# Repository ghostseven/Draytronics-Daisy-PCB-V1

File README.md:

# Draytronics-Daisy-PCB-V1

An open source macro pad with rotary encoders and under glow, designed to be easily built with (mostly) through hole components. More info / kits / PCB designs available at https://www.draytronics.co.uk/daisy

\

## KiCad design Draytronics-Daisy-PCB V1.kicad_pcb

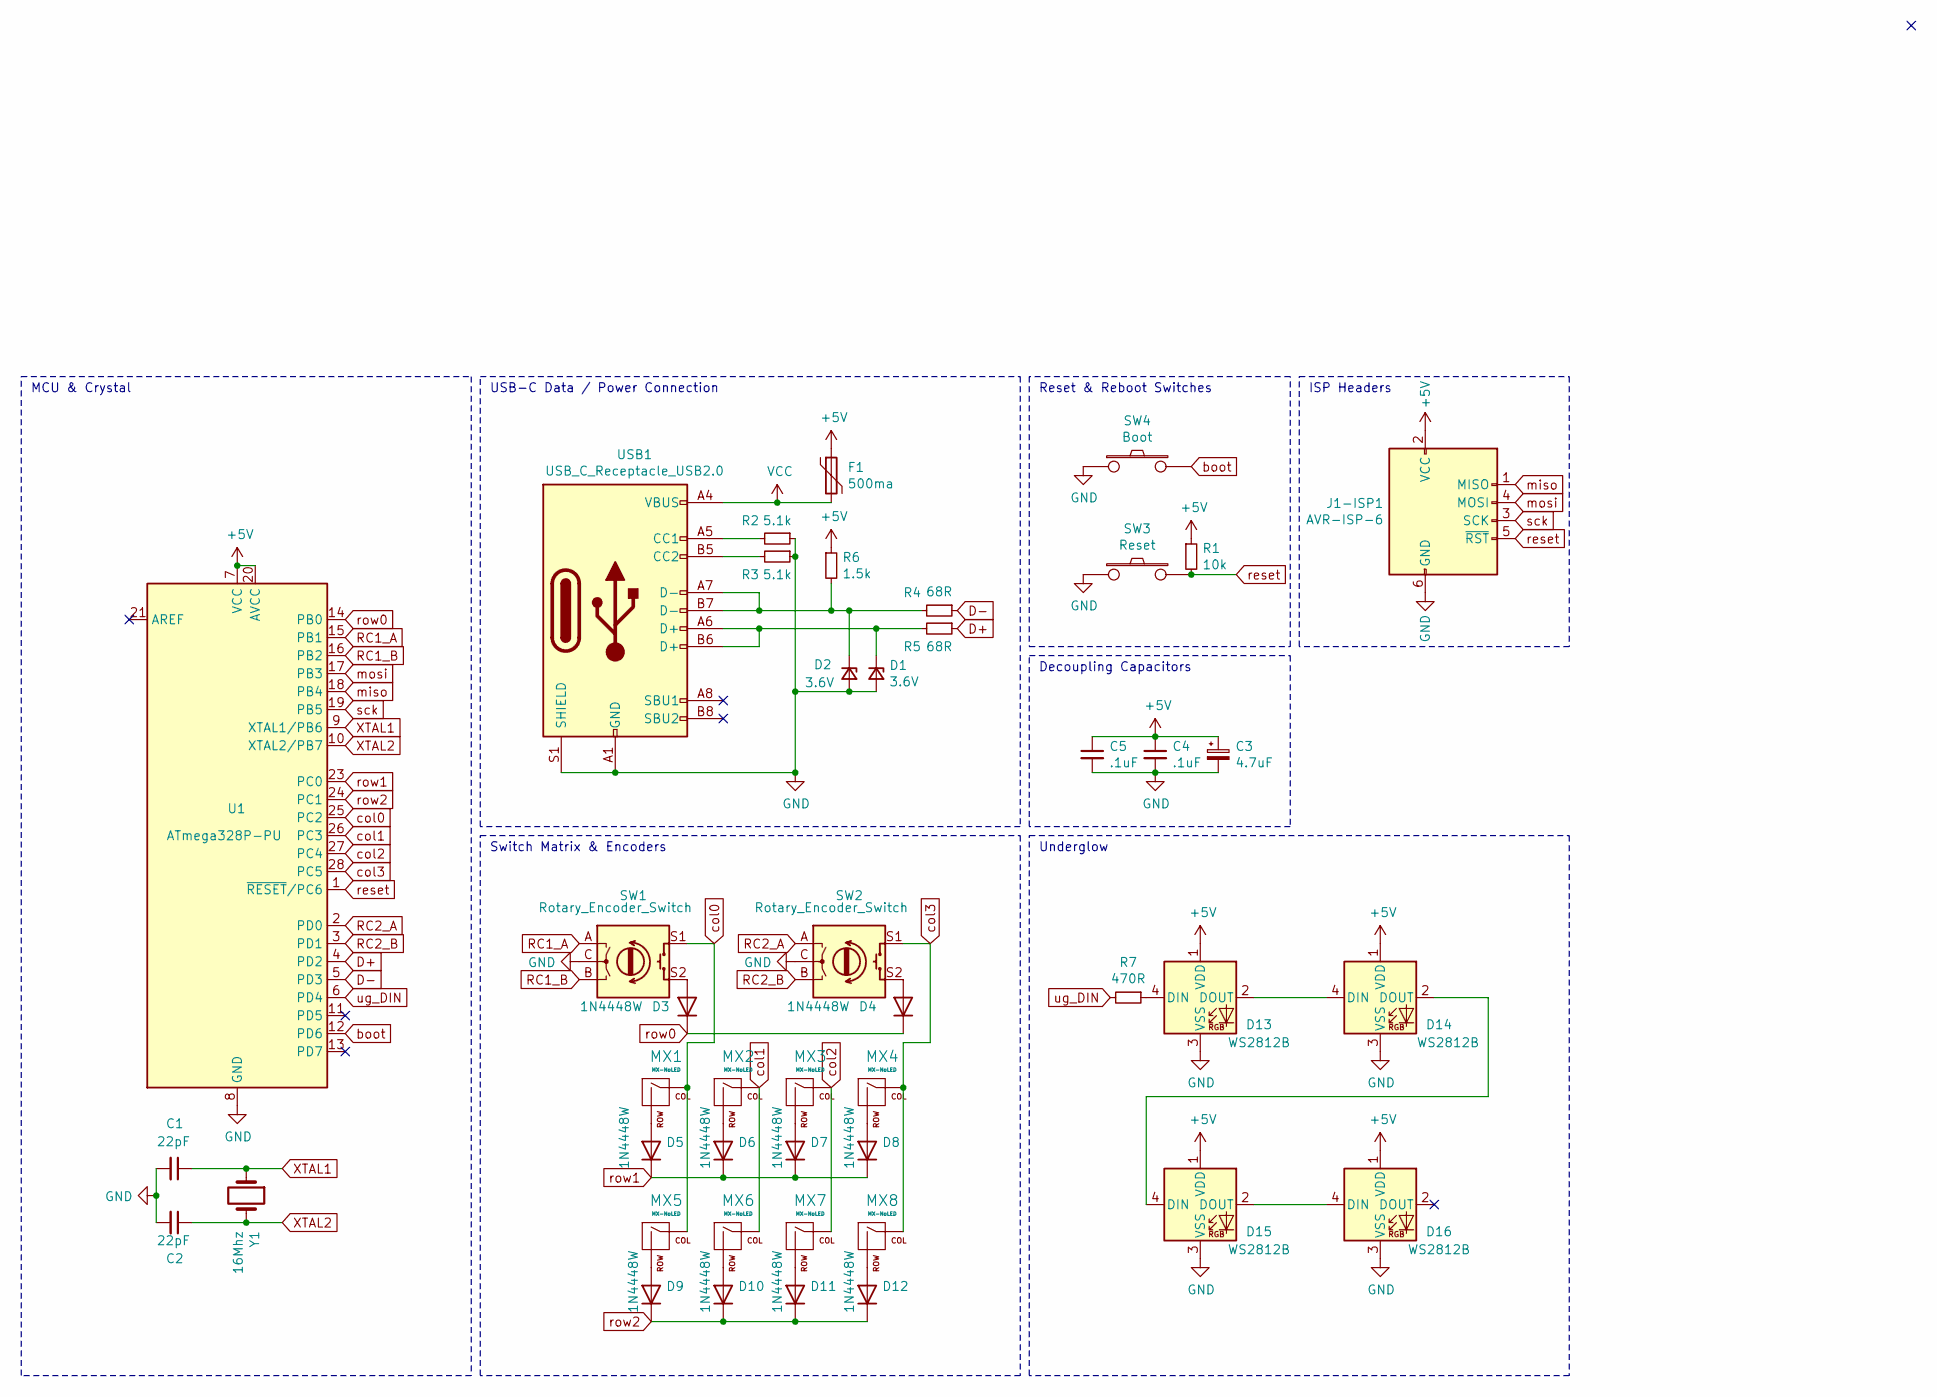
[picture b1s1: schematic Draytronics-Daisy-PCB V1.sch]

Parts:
C1, C2: 22pF; C_Disc_D3.0mm_W1.6mm_P2.50mm
C3: 4.7uF; CP_Radial_D4.0mm_P1.50mm
C4, C5: .1uF; C_Disc_D3.0mm_W1.6mm_P2.50mm
D1, D2: 3.6V; D_DO-35_SOD27_P5.08mm_Horizontal
D3, D4, D5, D6, D7, D8, D9, D10, D11, D12: 1N4448W; D_DO-35_SOD27_P5.08mm_Horizontal
D13, D14, D15, D16: WS2812B; LED_WS2812B_PLCC4_5.0x5.0mm_P3.2mm
F1: 500ma; polyfuse_5.1mm
J1-ISP1: AVR-ISP-6; IDC-Header_2x03_P2.54mm_Vertical
MX1, MX2, MX3, MX4, MX5, MX6, MX7, MX8: MX-NoLED; MXOnly-1U-NoLED
R1: 10k; R_Axial_DIN0204_L3.6mm_D1.6mm_P7.62mm_Horizontal
R2, R3: 5.1k; R_Axial_DIN0204_L3.6mm_D1.6mm_P7.62mm_Horizontal
R4, R5: 68R; R_Axial_DIN0204_L3.6mm_D1.6mm_P7.62mm_Horizontal
R6: 1.5k; R_Axial_DIN0204_L3.6mm_D1.6mm_P7.62mm_Horizontal
R7: 470R; R_Axial_DIN0204_L3.6mm_D1.6mm_P7.62mm_Horizontal
SW1, SW2: Rotary_Encoder_Switch; RotaryEncoder_Alps_EC11E-Switch_Vertical_H20mm
SW3: Reset; SW_PUSH_6mm
SW4: Boot; SW_PUSH_6mm
U1: ATmega328P-PU; DIP-28_W7.62mm
USB1: USB_C_Receptacle_USB2.0; USB_C_GCT_USB4085
Y1: 16Mhz; Crystal_HC49-U_Vertical

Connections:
+5V: C3.1, C4.1, C5.1, D13.1 (VDD), D14.1 (VDD), D15.1 (VDD), D16.1 (VDD), F1.1, J1-ISP1.2 (VCC), R1.1, R6.1, U1.7 (VCC), U1.20 (AVCC)
D+: R5.1, U1.4 (PD2)
D-: R4.1, U1.5 (PD3)
GND: C1.2, C2.2, C3.2, C4.2, C5.2, D1.2 (A), D2.2 (A), D13.3 (VSS), D14.3 (VSS), D15.3 (VSS), D16.3 (VSS), J1-ISP1.6 (GND), R2.1, R3.1, SW1.C, SW2.C, SW3.1, SW4.1, U1.8 (GND), U1.22 (GND), USB1.A1 (GND), USB1.A12 (GND), USB1.B1 (GND), USB1.B12 (GND), USB1.S1 (SHIELD)
unnamed: D1.1 (K), R5.2, USB1.A6 (D+), USB1.B6 (D+)
unnamed: D2.1 (K), R4.2, R6.2, USB1.A7 (D-), USB1.B7 (D-)
unnamed: D3.2 (A), SW1.S2
unnamed: D4.2 (A), SW2.S2
unnamed: D5.2 (A), MX1.2 (ROW)
unnamed: D6.2 (A), MX2.2 (ROW)
unnamed: D7.2 (A), MX3.2 (ROW)
unnamed: D8.2 (A), MX4.2 (ROW)
unnamed: D9.2 (A), MX5.2 (ROW)
unnamed: D10.2 (A), MX6.2 (ROW)
unnamed: D11.2 (A), MX7.2 (ROW)
unnamed: D12.2 (A), MX8.2 (ROW)
unnamed: D13.2 (DOUT), D14.4 (DIN)
unnamed: D13.4 (DIN), R7.1
unnamed: D14.2 (DOUT), D15.4 (DIN)
unnamed: D15.2 (DOUT), D16.4 (DIN)
unnamed: R2.2, USB1.A5 (CC1)
unnamed: R3.2, USB1.B5 (CC2)
RC1_A: SW1.A, U1.15 (PB1)
RC1_B: SW1.B, U1.16 (PB2)
RC2_A: SW2.A, U1.2 (PD0)
RC2_B: SW2.B, U1.3 (PD1)
VCC: F1.2, USB1.A4 (VBUS), USB1.A9 (VBUS), USB1.B4 (VBUS), USB1.B9 (VBUS)
XTAL1: C1.1, U1.9 (XTAL1/PB6), Y1.1
XTAL2: C2.1, U1.10 (XTAL2/PB7), Y1.2
boot: SW4.2, U1.12 (PD6)
col0: MX1.1 (COL), MX5.1 (COL), SW1.S1, U1.25 (PC2)
col1: MX2.1 (COL), MX6.1 (COL), U1.26 (PC3)
col2: MX3.1 (COL), MX7.1 (COL), U1.27 (PC4)
col3: MX4.1 (COL), MX8.1 (COL), SW2.S1, U1.28 (PC5)
miso: J1-ISP1.1 (MISO), U1.18 (PB4)
mosi: J1-ISP1.4 (MOSI), U1.17 (PB3)
reset: J1-ISP1.5 (~RST), R1.2, SW3.2, U1.1 (~RESET~/PC6)
row0: D3.1 (K), D4.1 (K), U1.14 (PB0)
row1: D5.1 (K), D6.1 (K), D7.1 (K), D8.1 (K), U1.23 (PC0)
row2: D9.1 (K), D10.1 (K), D11.1 (K), D12.1 (K), U1.24 (PC1)
sck: J1-ISP1.3 (SCK), U1.19 (PB5)
ug_DIN: R7.2, U1.6 (PD4)

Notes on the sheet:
USB-C Data / Power Connection
MCU & Crystal
Reset & Reboot Switches
ISP Headers
Decoupling Capacitors
Switch Matrix & Encoders
Underglow

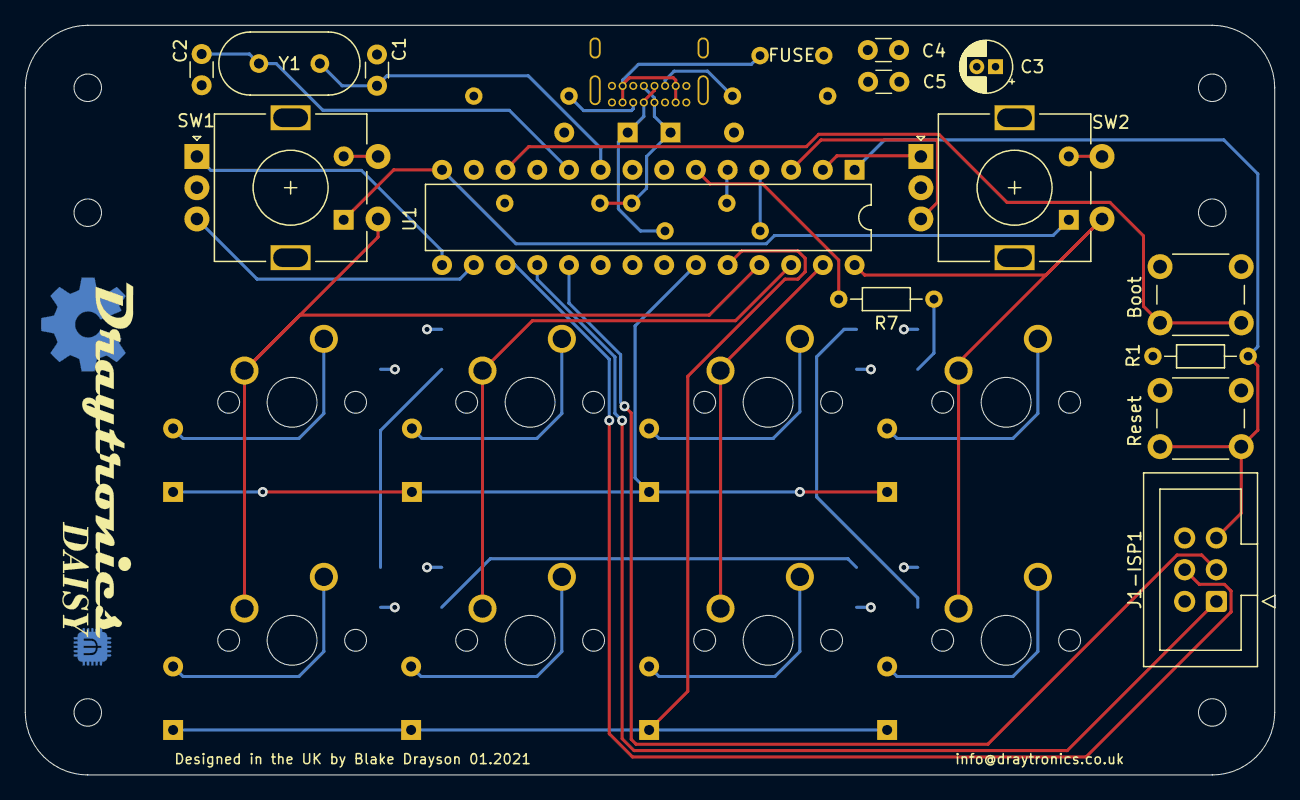
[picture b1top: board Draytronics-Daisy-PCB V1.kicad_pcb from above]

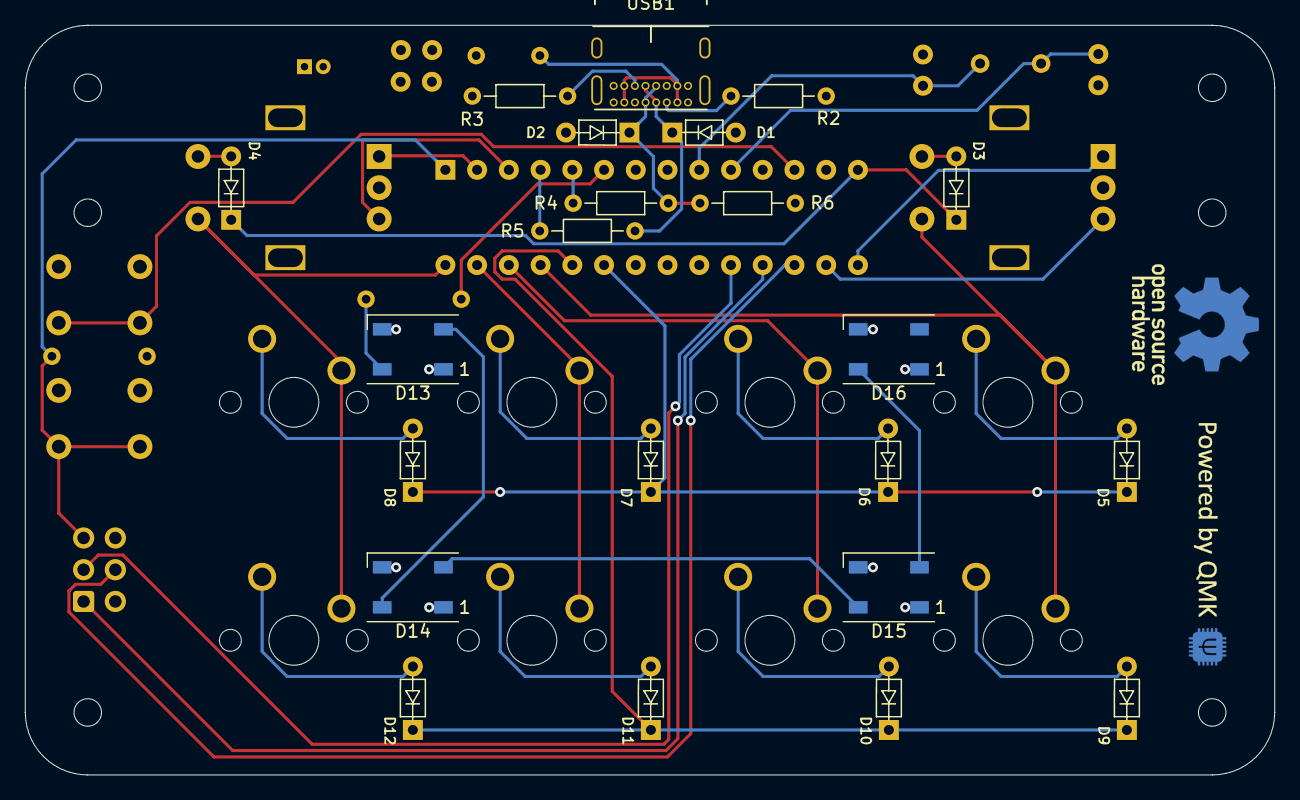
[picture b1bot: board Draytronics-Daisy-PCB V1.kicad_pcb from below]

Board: 4 copper layers, 100.0 x 60.0 mm, 45 parts (22 on the bottom side), 42 nets.

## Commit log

2020-12-29 Readme update.
2020-12-30 Added PCB renders
2021-03-12 First prod version
2021-12-30 added high profile case
    added .f3d and .stl of high profile case based off the original one released
